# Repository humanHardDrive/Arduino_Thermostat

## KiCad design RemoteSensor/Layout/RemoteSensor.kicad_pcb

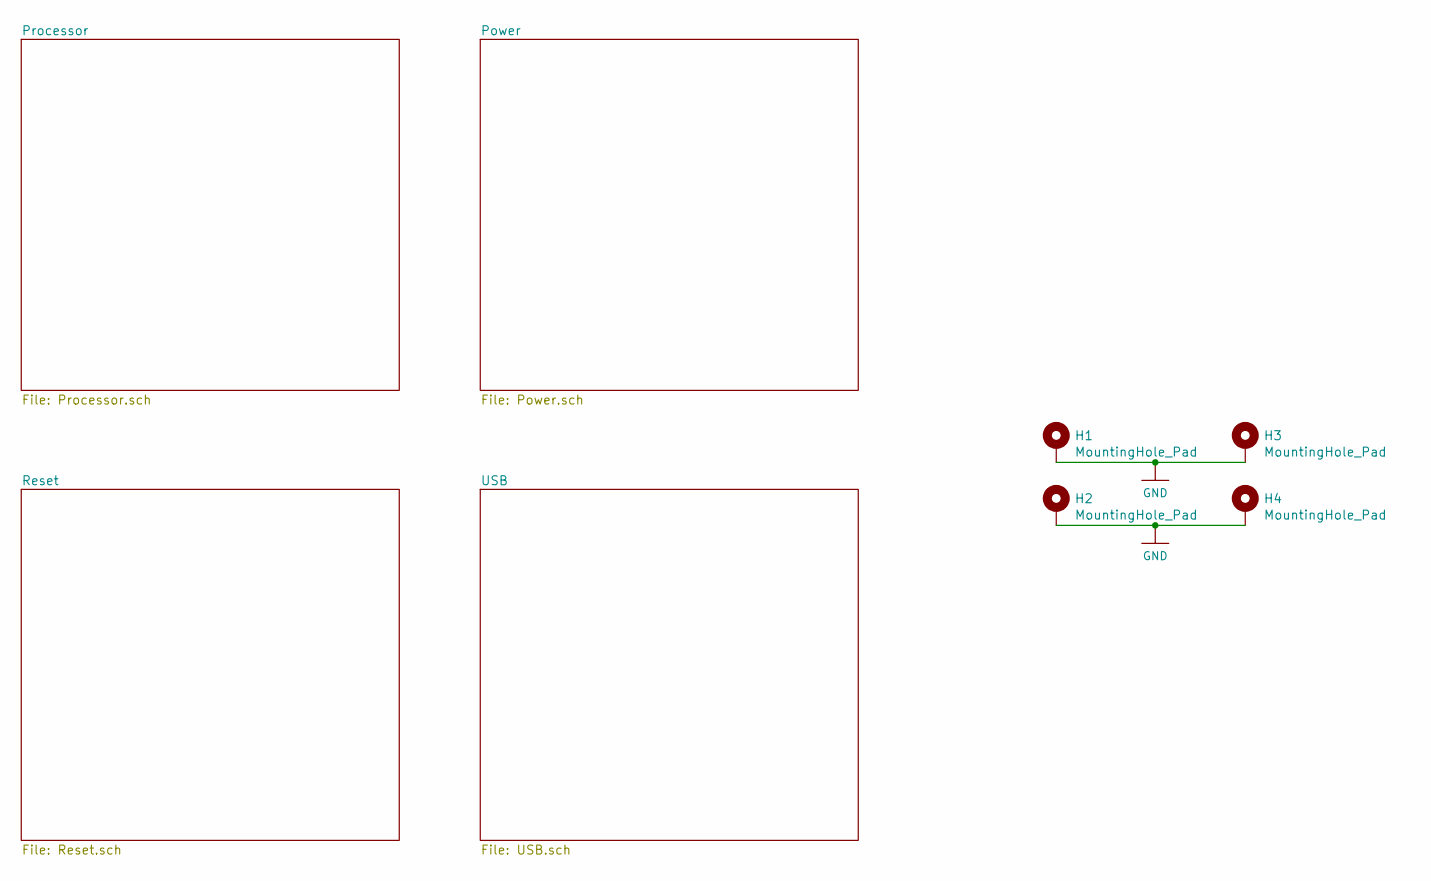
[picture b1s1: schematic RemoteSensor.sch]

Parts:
H1, H2, H3, H4: MountingHole_Pad; MountingHole_2.7mm_M2.5_DIN965_Pad

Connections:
GND: H1.1, H2.1, H3.1, H4.1; also elsewhere on the board

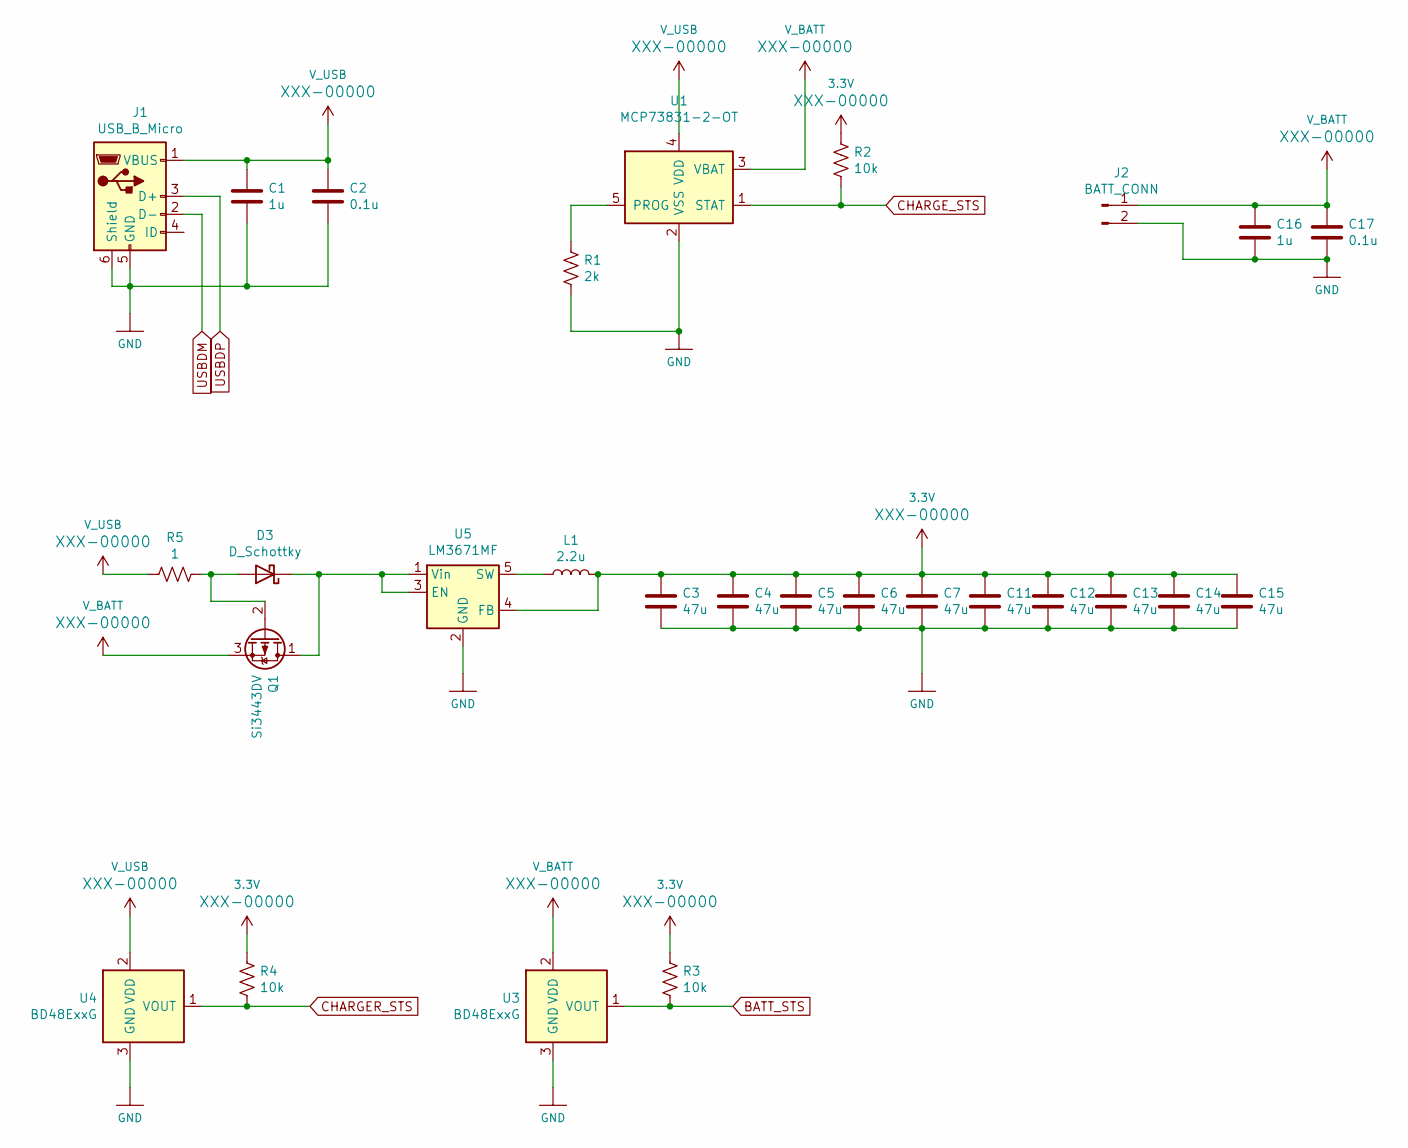
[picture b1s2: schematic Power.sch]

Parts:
C1, C16: 1u; C_0603_1608Metric_Pad1.05x0.95mm_HandSolder
C2, C17: 0.1u; C_0603_1608Metric_Pad1.05x0.95mm_HandSolder
C3, C4, C5, C6, C7, C11, C12, C13, C14, C15: 47u; C_0603_1608Metric_Pad1.05x0.95mm_HandSolder
D3: D_Schottky; D_SOD-123
J1: USB_B_Micro; USB_Micro-B_Molex_47346-0001
J2: BATT_CONN; JST_PH_S2B-PH-SM4-TB_1x02-1MP_P2.00mm_Horizontal
L1: 2.2u; L_Taiyo-Yuden_NR-30xx_HandSoldering
Q1: Si3443DV
R1: 2k; R_0603_1608Metric_Pad1.05x0.95mm_HandSolder
R2, R3, R4: 10k; R_0603_1608Metric_Pad1.05x0.95mm_HandSolder
R5: 1; R_0603_1608Metric_Pad1.05x0.95mm_HandSolder
U1: MCP73831-2-OT; SOT-23-5
U3, U4: BD48ExxG; SOT-23-5
U5: LM3671MF; TSOT-23-5

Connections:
3.3V: C3.1, C4.1, C5.1, C6.1, C7.1, C11.1, C12.1, C13.1, C14.1, C15.1, L1.2, R2.1, R3.1, R4.1, U5.4 (FB); also elsewhere on the board
BATT_STS: R3.2, U3.1 (VOUT); also elsewhere on the board
CHARGER_STS: R4.2, U4.1 (VOUT); also elsewhere on the board
CHARGE_STS: R2.2, U1.1 (STAT); also elsewhere on the board
GND: C1.2, C2.2, C3.2, C4.2, C5.2, C6.2, C7.2, C11.2, C12.2, C13.2, C14.2, C15.2, C16.2, C17.2, J1.5 (GND), J1.6 (Shield), J2.2, R1.2, U1.2 (VSS), U3.3 (GND), U4.3 (GND), U5.2 (GND); also elsewhere on the board
unnamed: D3.1 (K), Q1.1 (D), U5.1 (Vin), U5.3 (EN)
unnamed: D3.2 (A), Q1.2 (G), R5.1
unnamed: L1.1, U5.5 (SW)
unnamed: R1.1, U1.5 (PROG)
USBDM: J1.2 (D-); also elsewhere on the board
USBDP: J1.3 (D+); also elsewhere on the board
V_BATT: C16.1, C17.1, J2.1, Q1.3 (S), U1.3 (VBAT), U3.2 (VDD)
V_USB: C1.1, C2.1, J1.1 (VBUS), R5.2, U1.4 (VDD), U4.2 (VDD); also elsewhere on the board

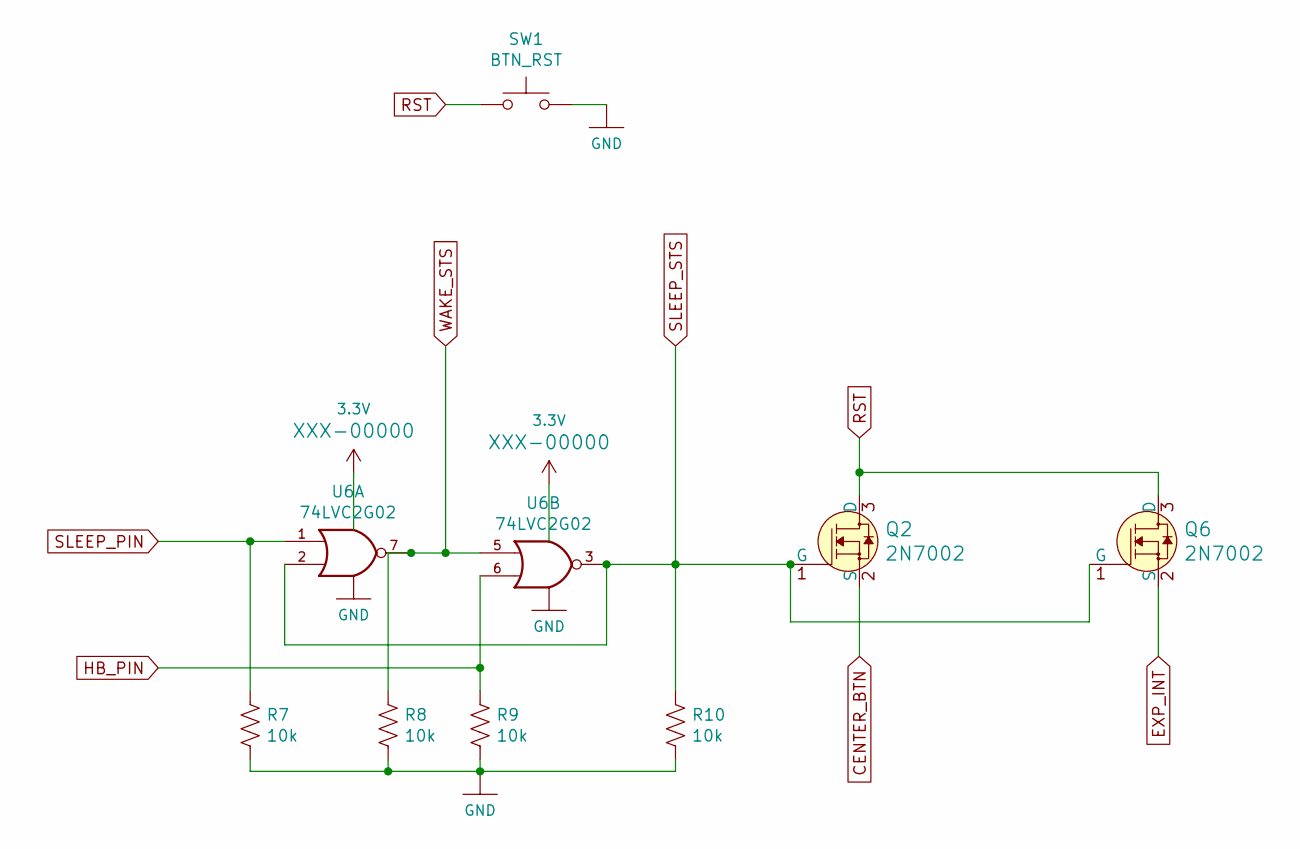
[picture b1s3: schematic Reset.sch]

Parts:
Q2, Q6: 2N7002; SOT-23-3; MPN 2N7002; Digi-Key_PN 2N7002NCT-ND
R7, R8, R9, R10: 10k; R_0603_1608Metric_Pad1.05x0.95mm_HandSolder
SW1: BTN_RST; SW_SPST_TL3342
U6: 74LVC2G02; VSSOP-8_2.3x2mm_P0.5mm

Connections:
3.3V: U6.8 (VCC); also elsewhere on the board
CENTER_BTN: Q2.2 (S); also elsewhere on the board
EXP_INT: Q6.2 (S); also elsewhere on the board
GND: R7.2, R8.2, R9.2, R10.2, SW1.2, U6.4 (GND); also elsewhere on the board
HB_PIN: R9.1, U6.6; also elsewhere on the board
RST: Q2.3 (D), Q6.3 (D), SW1.1; also elsewhere on the board
SLEEP_PIN: R7.1, U6.1; also elsewhere on the board
SLEEP_STS: Q2.1 (G), Q6.1 (G), R10.1, U6.2, U6.3
WAKE_STS: R8.1, U6.5, U6.7; also elsewhere on the board

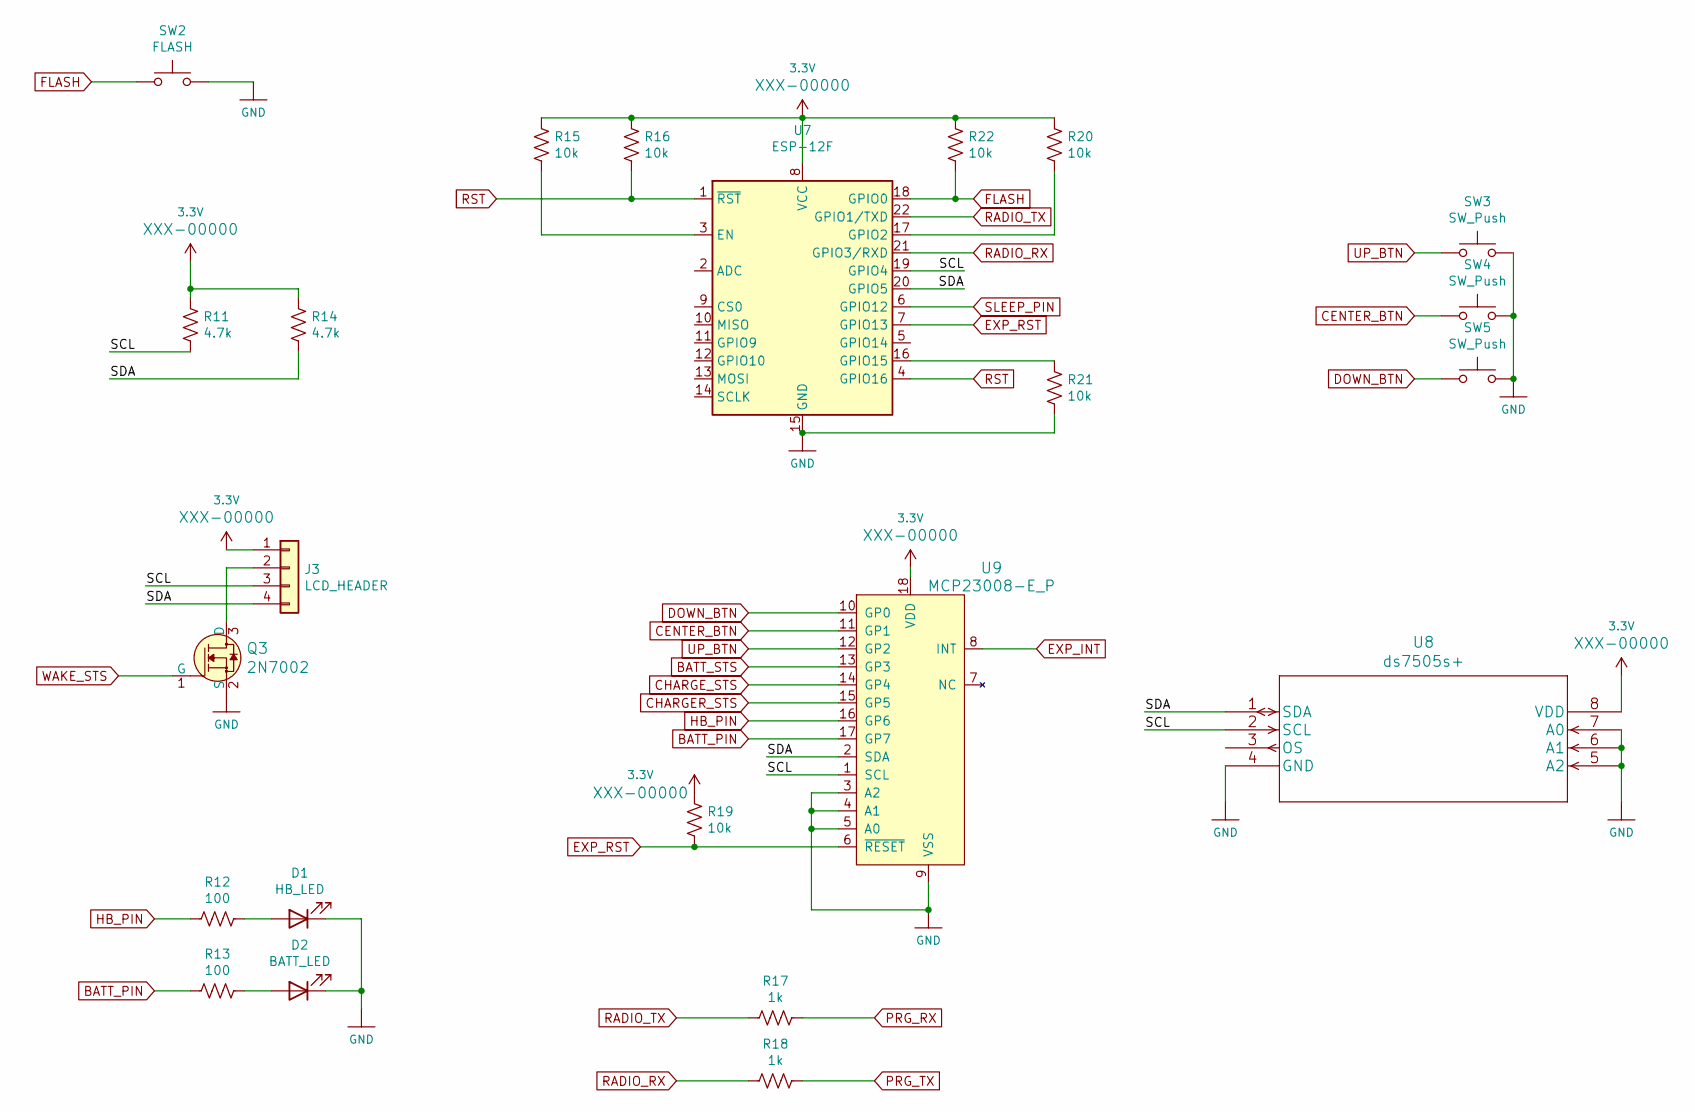
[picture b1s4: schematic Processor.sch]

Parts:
D1: HB_LED; LED_0603_1608Metric_Pad1.05x0.95mm_HandSolder
D2: BATT_LED; LED_0603_1608Metric_Pad1.05x0.95mm_HandSolder
J3: LCD_HEADER; PinSocket_1x04_P2.54mm_Vertical
Q3: 2N7002; SOT-23-3; MPN 2N7002; Digi-Key_PN 2N7002NCT-ND
R11, R14: 4.7k; R_0603_1608Metric_Pad1.05x0.95mm_HandSolder
R12, R13: 100; R_0603_1608Metric_Pad1.05x0.95mm_HandSolder
R15, R16, R19, R20, R21, R22: 10k; R_0603_1608Metric_Pad1.05x0.95mm_HandSolder
R17, R18: 1k; R_0603_1608Metric_Pad1.05x0.95mm_HandSolder
SW2: FLASH; SW_SPST_TL3342
SW3, SW4, SW5: SW_Push; KSS331GLFS
U7: ESP-12F; ESP-12E
U8: ds7505s+; SOIC-8_3.9x4.9mm_P1.27mm
U9: MCP23008-E_P; SOIC-18W_7.5x11.6mm_P1.27mm; MPN MCP23008-E/P; Digi-Key_PN MCP23008-E/P-ND

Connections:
3.3V: J3.1, R11.1, R14.1, R15.1, R16.1, R19.1, R20.1, R22.1, U7.8 (VCC), U8.8 (VDD), U9.18 (VDD); also elsewhere on the board
/Processor/SCL: J3.3, R11.2, U7.19 (GPIO4), U8.2 (SCL), U9.1 (SCL)
/Processor/SDA: J3.4, R14.2, U7.20 (GPIO5), U8.1 (SDA), U9.2 (SDA)
BATT_PIN: R13.2, U9.17 (GP7)
BATT_STS: U9.13 (GP3); also elsewhere on the board
CENTER_BTN: SW4.1, U9.11 (GP1); also elsewhere on the board
CHARGER_STS: U9.15 (GP5); also elsewhere on the board
CHARGE_STS: U9.14 (GP4); also elsewhere on the board
DOWN_BTN: SW5.1, U9.10 (GP0)
EXP_INT: U9.8 (INT); also elsewhere on the board
EXP_RST: R19.2, U7.7 (GPIO13), U9.6 (~RESET)
FLASH: R22.2, SW2.1, U7.18 (GPIO0)
GND: D1.1 (K), D2.1 (K), Q3.2 (S), R21.2, SW2.2, SW3.2, SW4.2, SW5.2, U7.15 (GND), U8.4 (GND), U8.5 (A2), U8.6 (A1), U8.7 (A0), U9.3 (A2), U9.4 (A1), U9.5 (A0), U9.9 (VSS); also elsewhere on the board
HB_PIN: R12.1, U9.16 (GP6); also elsewhere on the board
unnamed: D1.2 (A), R12.2
unnamed: D2.2 (A), R13.1
unnamed: J3.2, Q3.3 (D)
unnamed: R15.2, U7.3 (EN)
unnamed: R20.2, U7.17 (GPIO2)
unnamed: R21.1, U7.16 (GPIO15)
PRG_RX: R17.1; also elsewhere on the board
PRG_TX: R18.1; also elsewhere on the board
RADIO_RX: R18.2, U7.21 (GPIO3/RXD)
RADIO_TX: R17.2, U7.22 (GPIO1/TXD)
RST: R16.2, U7.1 (~RST), U7.4 (GPIO16); also elsewhere on the board
SLEEP_PIN: U7.6 (GPIO12); also elsewhere on the board
UP_BTN: SW3.1, U9.12 (GP2)
WAKE_STS: Q3.1 (G); also elsewhere on the board

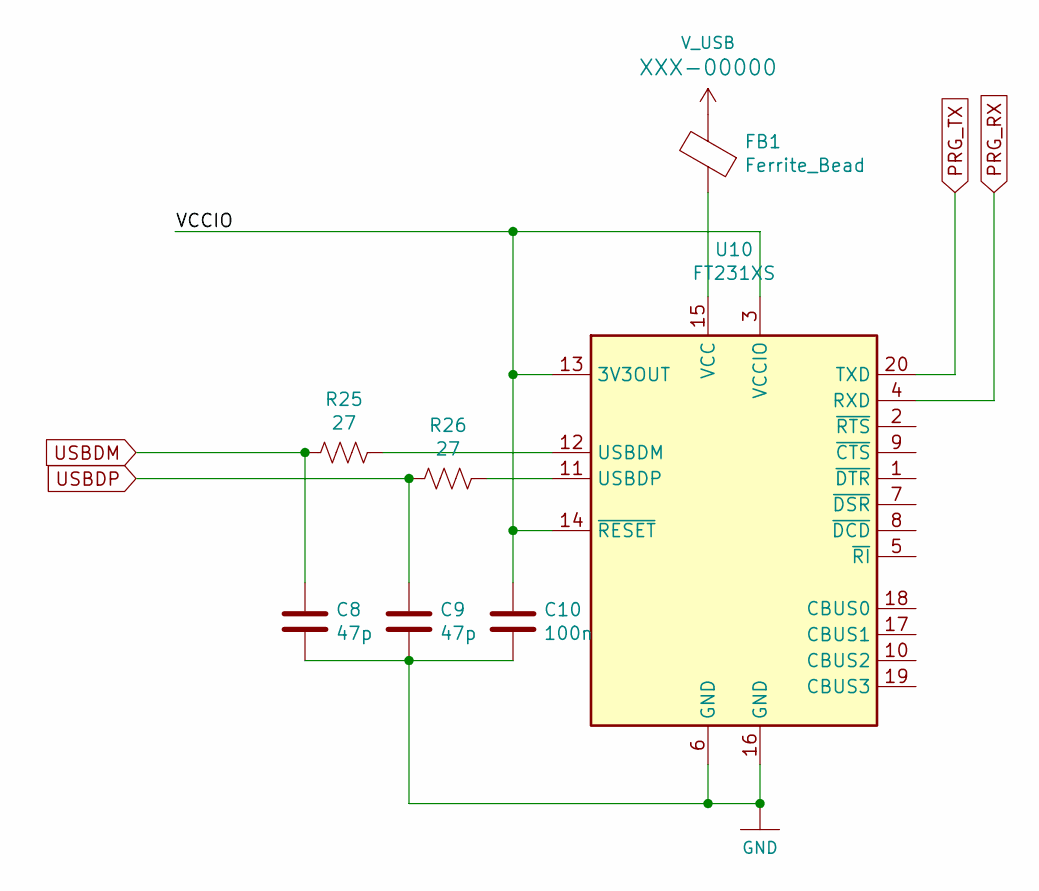
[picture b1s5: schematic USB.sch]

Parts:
C8, C9: 47p; C_0603_1608Metric_Pad1.05x0.95mm_HandSolder
C10: 100n; C_0603_1608Metric_Pad1.05x0.95mm_HandSolder
FB1: Ferrite_Bead; R_0603_1608Metric_Pad1.05x0.95mm_HandSolder
R25, R26: 27; R_0603_1608Metric_Pad1.05x0.95mm_HandSolder
U10: FT231XS; SSOP-20_3.9x8.7mm_P0.635mm

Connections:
/USB/VCCIO: C10.1, U10.3 (VCCIO), U10.13 (3V3OUT), U10.14 (~RESET)
GND: C8.2, C9.2, C10.2, U10.6 (GND), U10.16 (GND); also elsewhere on the board
unnamed: FB1.1, U10.15 (VCC)
unnamed: R25.1, U10.12 (USBDM)
unnamed: R26.1, U10.11 (USBDP)
PRG_RX: U10.4 (RXD); also elsewhere on the board
PRG_TX: U10.20 (TXD); also elsewhere on the board
USBDM: C8.1, R25.2; also elsewhere on the board
USBDP: C9.1, R26.2; also elsewhere on the board
V_USB: FB1.2; also elsewhere on the board

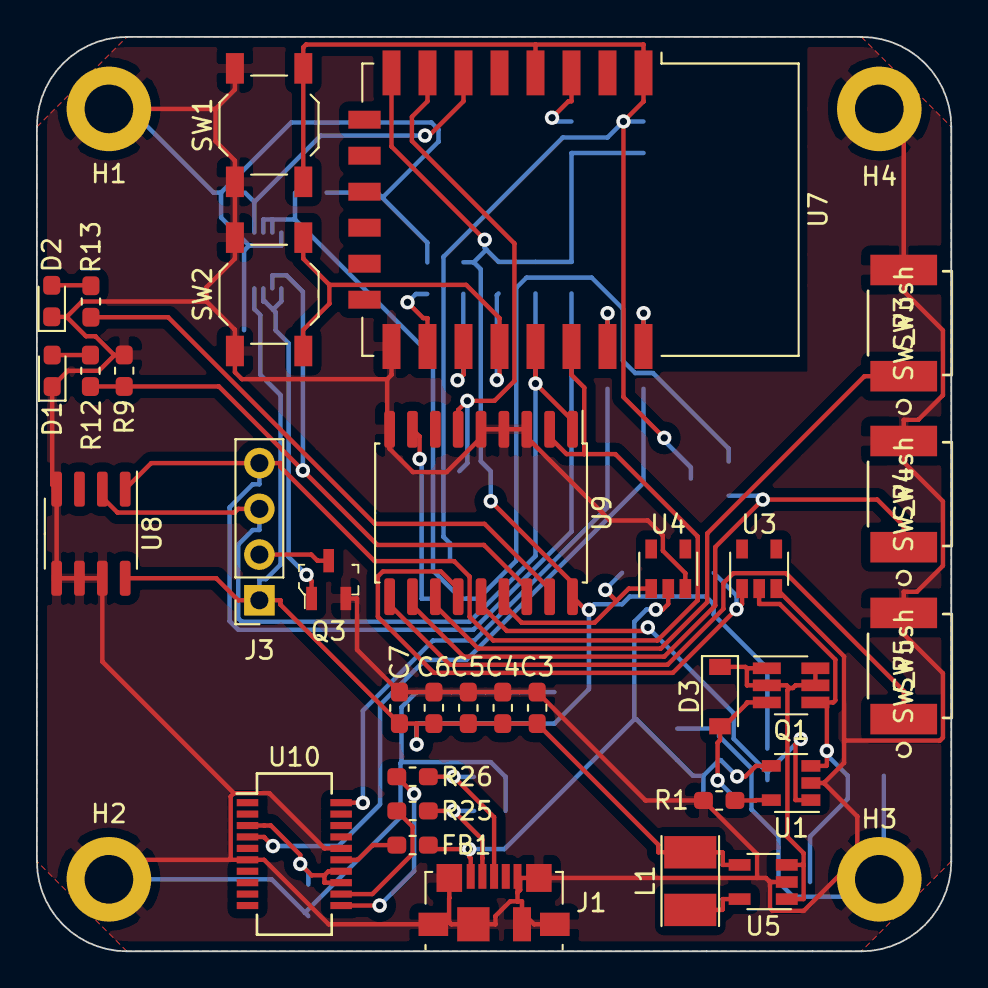
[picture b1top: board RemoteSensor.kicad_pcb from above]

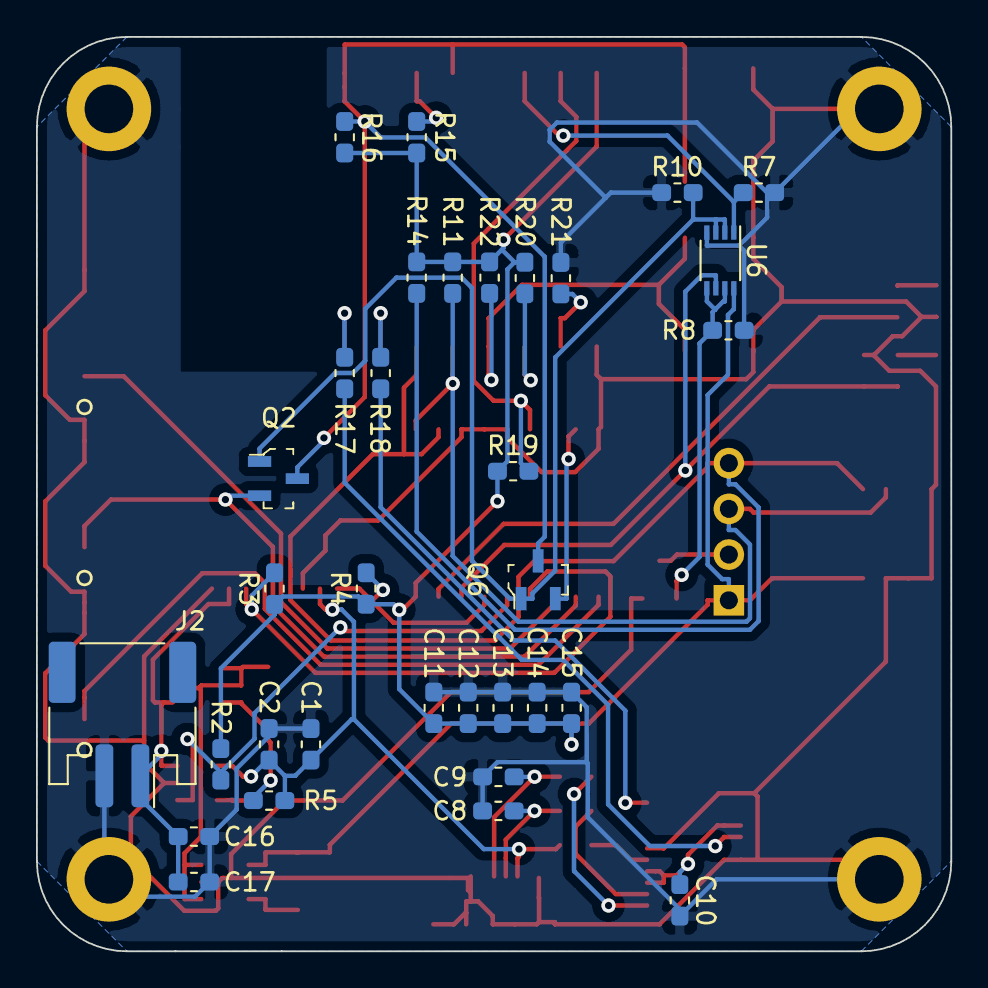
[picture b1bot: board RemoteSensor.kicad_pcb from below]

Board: 2 copper layers, 50.8 x 50.8 mm, 70 parts (33 on the bottom side), 41 nets.

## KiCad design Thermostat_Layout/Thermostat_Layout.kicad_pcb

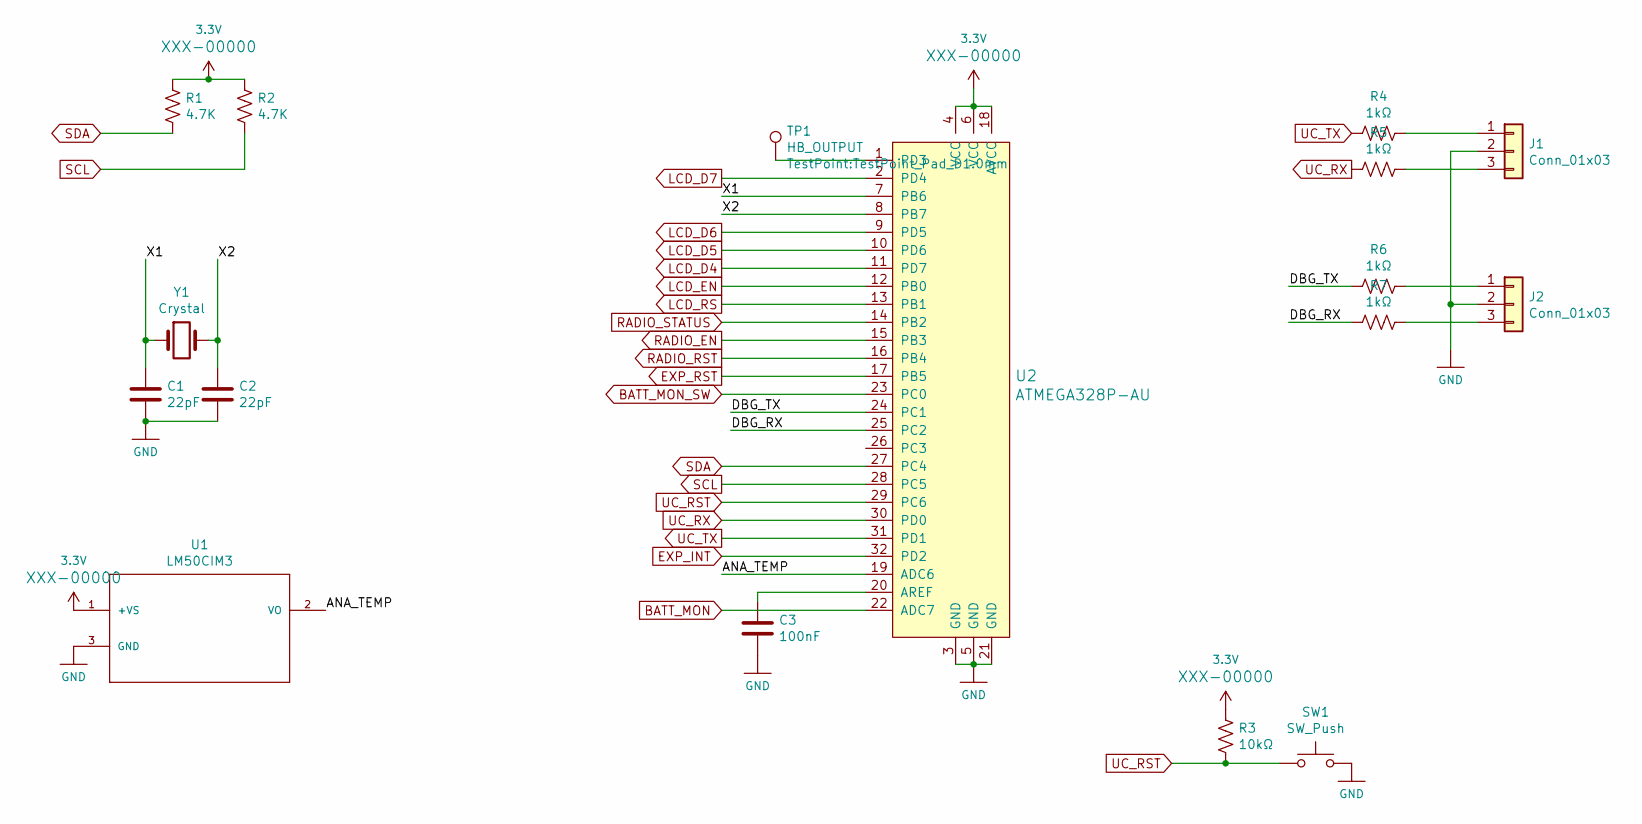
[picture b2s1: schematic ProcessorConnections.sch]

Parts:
C1, C2: 22pF; C_0402_1005Metric
C3: 100nF; C_0402_1005Metric
J1, J2: Conn_01x03; JST_PH_S3B-PH-SM4-TB_1x03-1MP_P2.00mm_Horizontal
R1, R2: 4.7K; R_0402_1005Metric
R3: 10kΩ; R_0402_1005Metric
R4, R5, R6, R7: 1kΩ; R_0402_1005Metric
SW1: SW_Push; SW_SPST_TL3342
TP1: HB_OUTPUT; TestPoint_Pad_D1.0mm
U1: LM50CIM3; SOT95P260X110-3N
U2: ATMEGA328P-AU; TQFP-32_7x7mm; MPN ATMEGA328P-AU; Digi-Key_PN ATMEGA328P-AU-ND
Y1: Crystal; Crystal_SMD_SeikoEpson_MC405-2Pin_9.6x4.1mm

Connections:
3.3V: R1.1, R2.1, R3.1, U1.1 (+VS), U2.4 (VCC), U2.6 (VCC), U2.18 (AVCC); also elsewhere on the board
/ProcessorConnections/ANA_TEMP: U1.2 (VO), U2.19 (ADC6)
/ProcessorConnections/DBG_RX: R7.2, U2.25 (PC2)
/ProcessorConnections/DBG_TX: R6.2, U2.24 (PC1)
/ProcessorConnections/X1: C1.1, U2.7 (PB6), Y1.1
/ProcessorConnections/X2: C2.1, U2.8 (PB7), Y1.2
BATT_MON: U2.22 (ADC7); also elsewhere on the board
EXP_INT: U2.32 (PD2); also elsewhere on the board
EXP_RST: U2.17 (PB5); also elsewhere on the board
GND: C1.2, C2.2, C3.2, J1.2, J2.2, SW1.2, U1.3 (GND), U2.3 (GND), U2.5 (GND), U2.21 (GND); also elsewhere on the board
LCD_D4: U2.11 (PD7); also elsewhere on the board
LCD_D5: U2.10 (PD6); also elsewhere on the board
LCD_D6: U2.9 (PD5); also elsewhere on the board
LCD_D7: U2.2 (PD4); also elsewhere on the board
LCD_EN: U2.12 (PB0); also elsewhere on the board
LCD_RS: U2.13 (PB1); also elsewhere on the board
unnamed: C3.1, U2.20 (AREF)
unnamed: J1.1, R4.1
unnamed: J1.3, R5.1
unnamed: J2.1, R6.1
unnamed: J2.3, R7.1
unnamed: TP1.1, U2.1 (PD3)
RADIO_EN: U2.15 (PB3); also elsewhere on the board
RADIO_RST: U2.16 (PB4); also elsewhere on the board
RADIO_STATUS: U2.14 (PB2); also elsewhere on the board
SCL: R2.2, U2.28 (PC5); also elsewhere on the board
SDA: R1.2, U2.27 (PC4); also elsewhere on the board
UC_RST: R3.2, SW1.1, U2.29 (PC6)
UC_RX: R5.2, U2.30 (PD0); also elsewhere on the board
UC_TX: R4.2, U2.31 (PD1); also elsewhere on the board

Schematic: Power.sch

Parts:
C4: 10uF; C_0402_1005Metric
C5, C6: 1uF; C_0402_1005Metric
C7: 0.1uF; C_0402_1005Metric
J3: Conn_01x02_Male; JST_PH_S2B-PH-SM4-TB_1x02-1MP_P2.00mm_Horizontal
R8: 220k; R_0402_1005Metric
R9: 100k; R_0402_1005Metric
U3: TSR_1-2433; Converter_DCDC_TRACO_TSR-1_THT

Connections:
3.3V: C6.1, C7.1, U3.3 (Vout); also elsewhere on the board
+9V: C4.1, C5.1, J3.1, R8.1, U3.1 (Vin)
BATT_MON: R8.2, R9.1; also elsewhere on the board
GND: C4.2, C5.2, C6.2, C7.2, J3.2, R9.2, U3.2 (GND); also elsewhere on the board

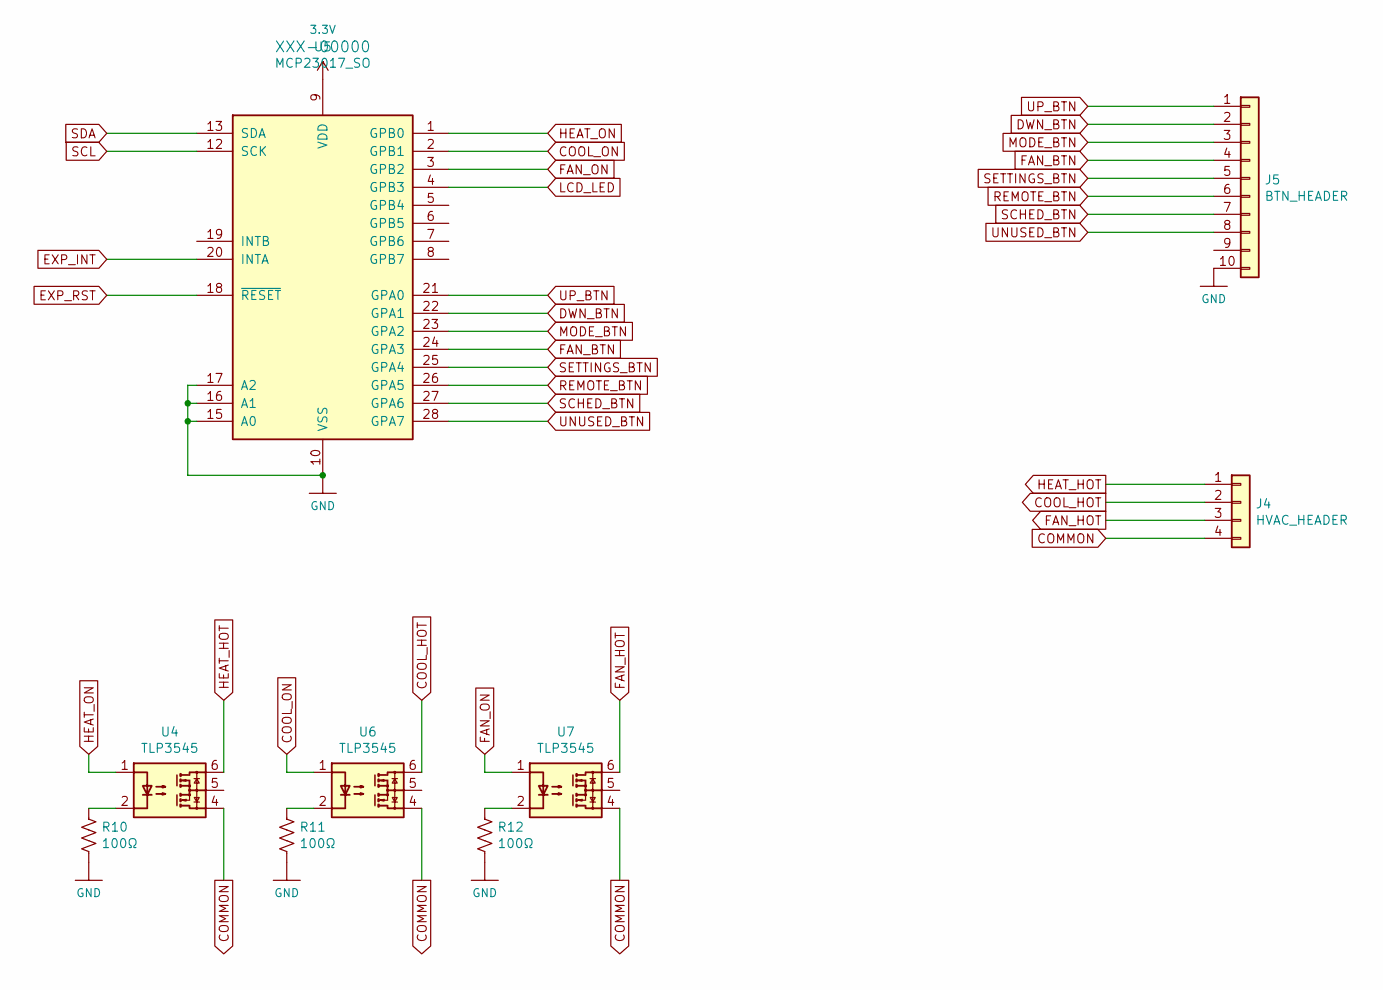
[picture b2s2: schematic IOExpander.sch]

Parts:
J4: HVAC_HEADER; TerminalBlock_TE_282834-4_1x04_P2.54mm_Horizontal
J5: BTN_HEADER; JST_PH_S10B-PH-SM4-TB_1x10-1MP_P2.00mm_Horizontal
R10, R11, R12: 100Ω; R_0402_1005Metric
U4, U6, U7: TLP3545; DIP-6_W7.62mm
U5: MCP23017_SO; SOIC-28W_7.5x17.9mm_P1.27mm

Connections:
3.3V: U5.9 (VDD); also elsewhere on the board
COMMON: J4.4, U4.4, U6.4, U7.4
COOL_HOT: J4.2, U6.6
COOL_ON: U5.2 (GPB1), U6.1
DWN_BTN: J5.2, U5.22 (GPA1)
EXP_INT: U5.20 (INTA); also elsewhere on the board
EXP_RST: U5.18 (~RESET~); also elsewhere on the board
FAN_BTN: J5.4, U5.24 (GPA3)
FAN_HOT: J4.3, U7.6
FAN_ON: U5.3 (GPB2), U7.1
GND: J5.10, R10.2, R11.2, R12.2, U5.10 (VSS), U5.15 (A0), U5.16 (A1), U5.17 (A2); also elsewhere on the board
HEAT_HOT: J4.1, U4.6
HEAT_ON: U4.1, U5.1 (GPB0)
LCD_LED: U5.4 (GPB3); also elsewhere on the board
MODE_BTN: J5.3, U5.23 (GPA2)
unnamed: R10.1, U4.2
unnamed: R11.1, U6.2
unnamed: R12.1, U7.2
REMOTE_BTN: J5.6, U5.26 (GPA5)
SCHED_BTN: J5.7, U5.27 (GPA6)
SCL: U5.12 (SCK); also elsewhere on the board
SDA: U5.13 (SDA); also elsewhere on the board
SETTINGS_BTN: J5.5, U5.25 (GPA4)
UNUSED_BTN: J5.8, U5.28 (GPA7)
UP_BTN: J5.1, U5.21 (GPA0)

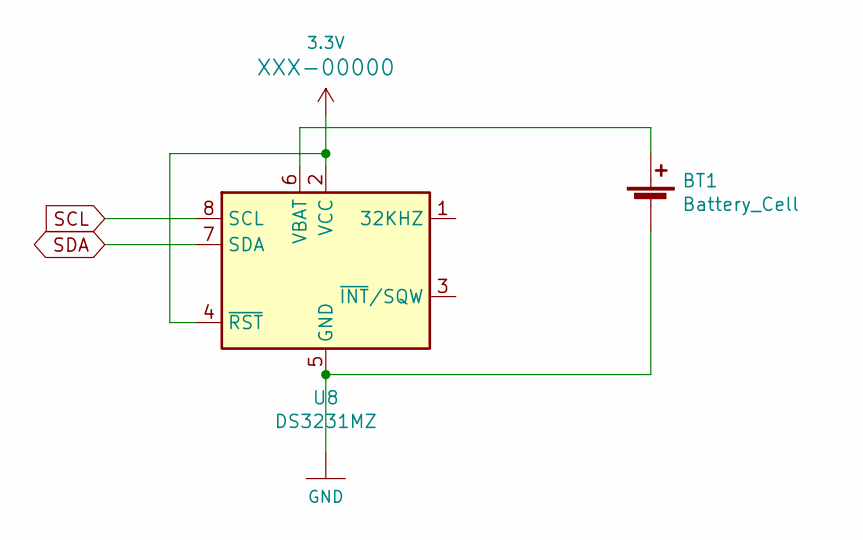
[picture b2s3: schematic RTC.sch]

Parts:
BT1: Battery_Cell; BatteryHolder_Keystone_3000_1x12mm
U8: DS3231MZ; SOIC-8_3.9x4.9mm_P1.27mm

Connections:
3.3V: U8.2 (VCC), U8.4 (~RST); also elsewhere on the board
GND: BT1.2 (-), U8.5 (GND); also elsewhere on the board
unnamed: BT1.1 (+), U8.6 (VBAT)
SCL: U8.8 (SCL); also elsewhere on the board
SDA: U8.7 (SDA); also elsewhere on the board

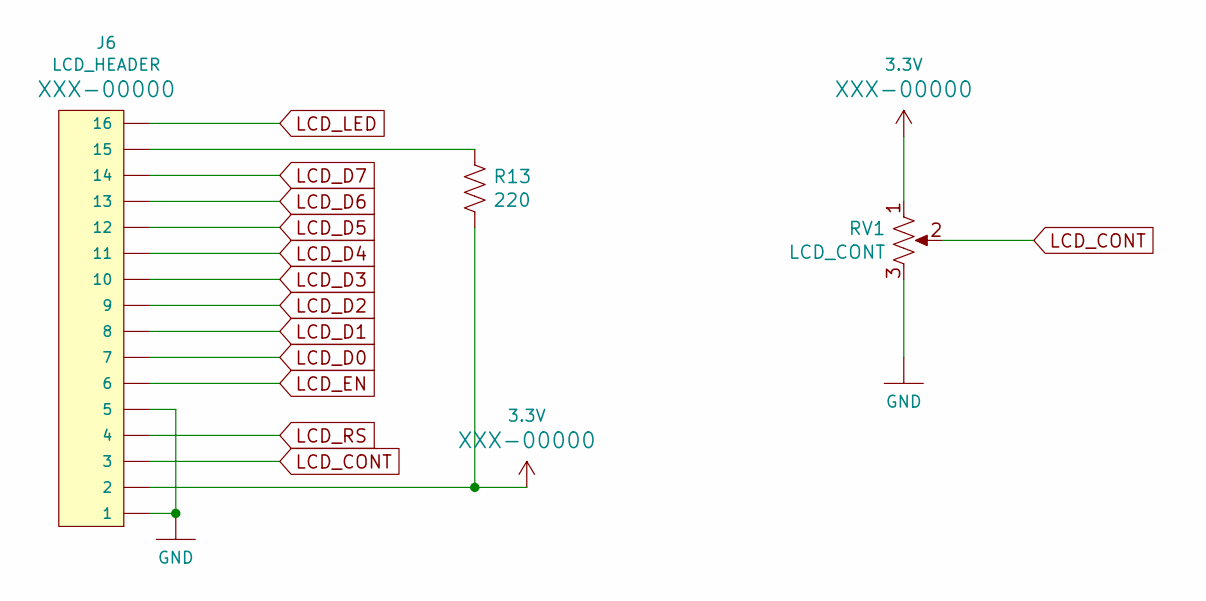
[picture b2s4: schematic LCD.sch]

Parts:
J6: LCD_HEADER; PinHeader_1x16_P2.54mm_Vertical
R13: 220; 0402
RV1: LCD_CONT; Potentiometer_Bourns_TC33X_Vertical

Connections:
3.3V: J6.2, R13.2, RV1.1; also elsewhere on the board
GND: J6.1, J6.5, RV1.3; also elsewhere on the board
LCD_CONT: J6.3, RV1.2
LCD_D4: J6.11; also elsewhere on the board
LCD_D5: J6.12; also elsewhere on the board
LCD_D6: J6.13; also elsewhere on the board
LCD_D7: J6.14; also elsewhere on the board
LCD_EN: J6.6; also elsewhere on the board
LCD_LED: J6.16; also elsewhere on the board
LCD_RS: J6.4; also elsewhere on the board
unnamed: J6.15, R13.1

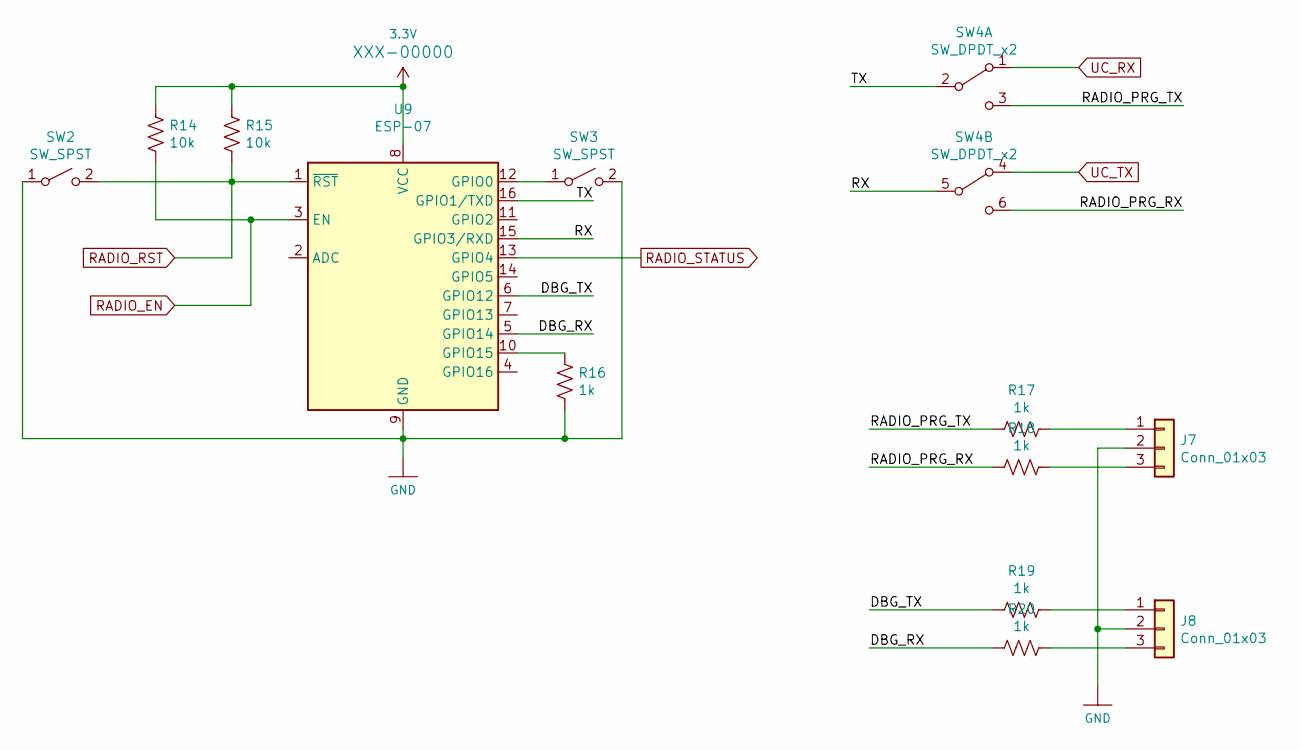
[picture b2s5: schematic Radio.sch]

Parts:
J7, J8: Conn_01x03; JST_PH_S3B-PH-SM4-TB_1x03-1MP_P2.00mm_Horizontal
R14, R15: 10k; R_0402_1005Metric
R16, R17, R18, R19, R20: 1k; R_0402_1005Metric
SW2, SW3: SW_SPST; SW_SPST_TL3342
SW4: SW_DPDT_x2
U9: ESP-07

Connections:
3.3V: R14.1, R15.1, U9.8 (VCC); also elsewhere on the board
/Radio/DBG_RX: R20.2, U9.5 (GPIO14)
/Radio/DBG_TX: R19.2, U9.6 (GPIO12)
/Radio/RADIO_PRG_RX: R18.2, SW4.6 (C)
/Radio/RADIO_PRG_TX: R17.2, SW4.3 (C)
/Radio/RX: SW4.5 (B), U9.15 (GPIO3/RXD)
/Radio/TX: SW4.2 (B), U9.16 (GPIO1/TXD)
GND: J7.2, J8.2, R16.2, SW2.1 (A), SW3.2 (B), U9.9 (GND); also elsewhere on the board
unnamed: J7.1, R17.1
unnamed: J7.3, R18.1
unnamed: J8.1, R19.1
unnamed: J8.3, R20.1
unnamed: R16.1, U9.10 (GPIO15)
unnamed: SW3.1 (A), U9.12 (GPIO0)
RADIO_EN: R14.2, U9.3 (EN); also elsewhere on the board
RADIO_RST: R15.2, SW2.2 (B), U9.1 (~RST); also elsewhere on the board
RADIO_STATUS: U9.13 (GPIO4); also elsewhere on the board
UC_RX: SW4.1 (A); also elsewhere on the board
UC_TX: SW4.4 (A); also elsewhere on the board

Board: 2 copper layers, 55 parts (10 on the bottom side), 65 nets, no tracks yet.

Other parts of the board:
H1, H2, H3: MountingHole; MountingHole_2.2mm_M2_DIN965_Pad

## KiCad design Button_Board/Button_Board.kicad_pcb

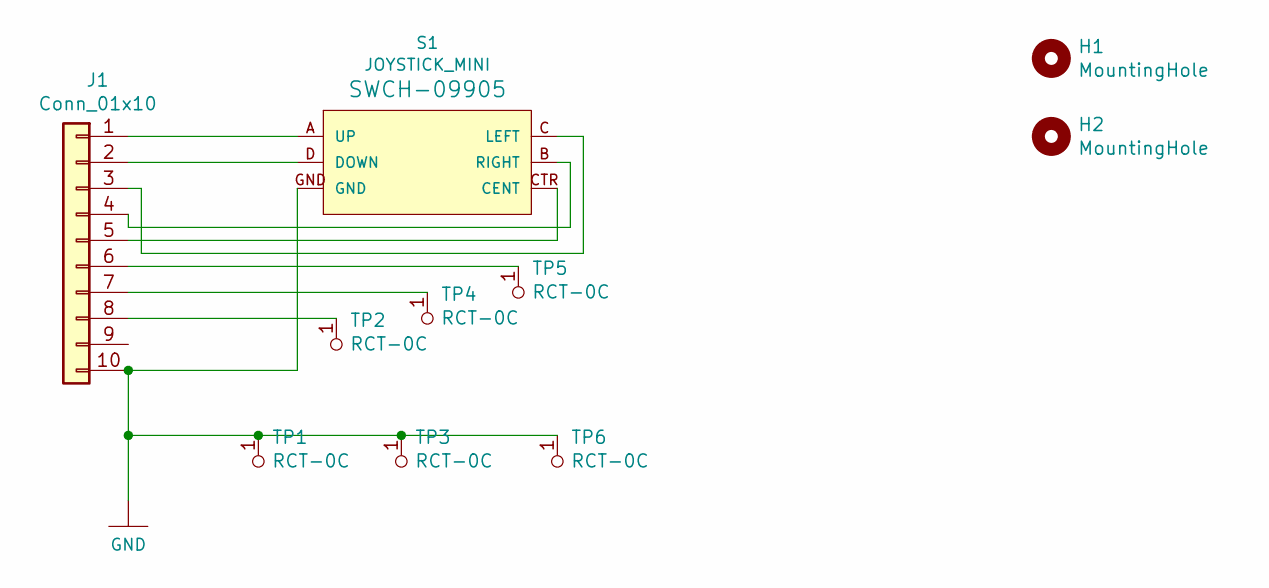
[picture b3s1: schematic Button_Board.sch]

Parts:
H1, H2: MountingHole; MountingHole_2.2mm_M2_ISO7380_Pad
J1: Conn_01x10; JST_PH_B10B-PH-SM4-TB_1x10-1MP_P2.00mm_Vertical
S1: JOYSTICK_MINI
TP1, TP2, TP3, TP4, TP5, TP6: RCT-0C; PROBE_PAD_0805; MPN RCT-0C; Digi-Key_PN A106144CT-ND

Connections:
GND: J1.10, S1.GND, TP1.1, TP3.1, TP6.1
unnamed: J1.1, S1.A (UP)
unnamed: J1.2, S1.D (DOWN)
unnamed: J1.3, S1.C (LEFT)
unnamed: J1.4, S1.B (RIGHT)
unnamed: J1.5, S1.CTR (CENT)
unnamed: J1.6, TP5.1
unnamed: J1.7, TP4.1
unnamed: J1.8, TP2.1

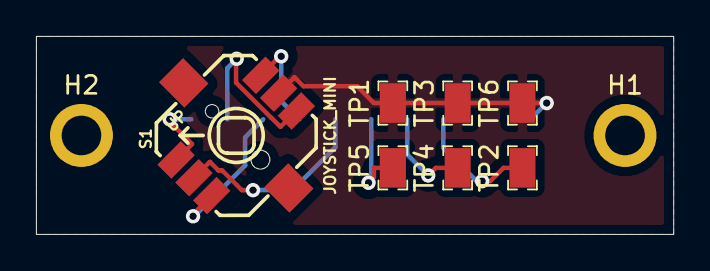
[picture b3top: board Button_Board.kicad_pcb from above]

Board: 2 copper layers, 35.4 x 11.0 mm, 10 parts (1 on the bottom side), 9 nets.

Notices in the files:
parts and their libraries:
Copyright 2016 Accelerated Designs. All rights reserved.
